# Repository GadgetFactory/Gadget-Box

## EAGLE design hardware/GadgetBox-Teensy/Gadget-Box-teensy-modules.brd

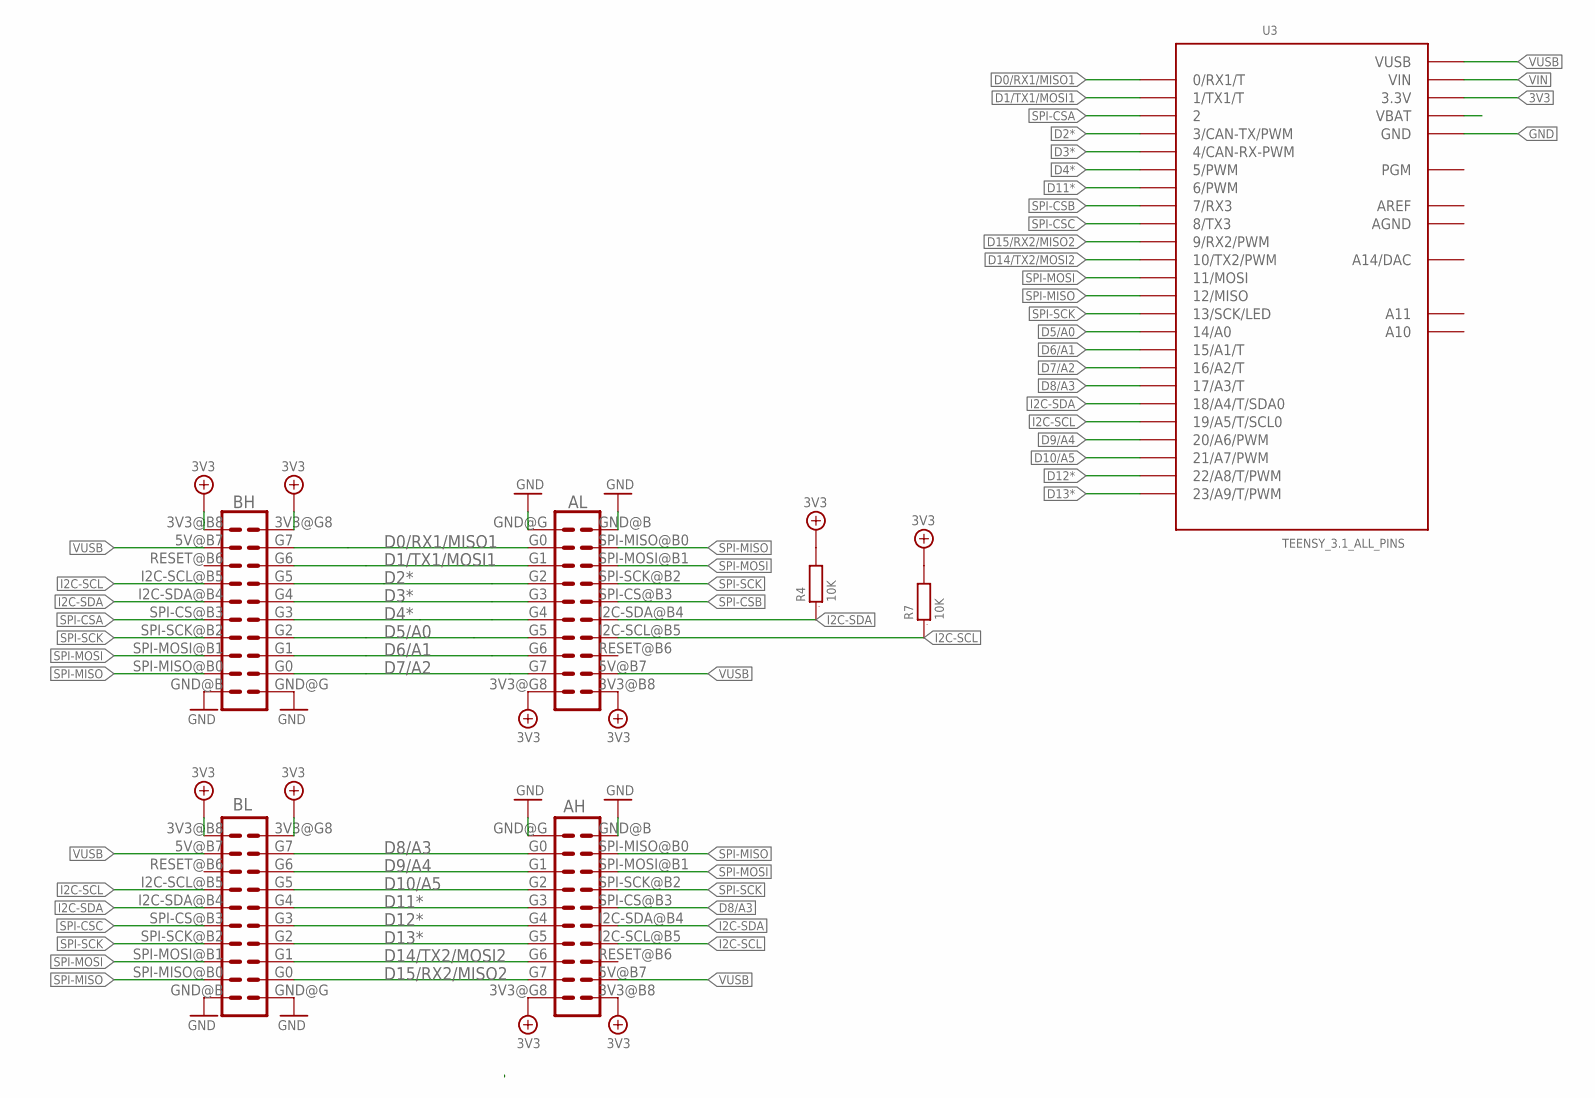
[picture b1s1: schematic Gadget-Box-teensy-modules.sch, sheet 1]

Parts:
AH: ECOGECOG_SLOT_ALT1; ECOG_ALT1; PARTNO PPPC102LFBN-RC,SULLINS CONNECTOR SOLUTI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
AL: ECOGECOG_SLOT_ALT1; ECOG_ALT1; PARTNO PPPC102LFBN-RC,SULLINS CONNECTOR SOLUTI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
BH: ECOGECOG_SLOT_ALT1; ECOG_ALT1; PARTNO PPPC102LFBN-RC,SULLINS CONNECTOR SOLUTI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
BL: ECOGECOG_SLOT_ALT1; ECOG_ALT1; PARTNO PPPC102LFBN-RC,SULLINS CONNECTOR SOLUTI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
R4, R7: 10K; 0603; PARTNO RC0603JR-0710KL,YAGEO (VA),dk,311-10KGR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
U3: TEENSY_3.1_ALL_PINS; TEENSY3-ALL_PINS

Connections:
3V3: AH.3V3@B8 (3V3), AH.3V3@G8 (3V3), AL.3V3@B8 (3V3), AL.3V3@G8 (3V3), BH.3V3@B8 (3V3), BH.3V3@G8 (3V3), BL.3V3@B8 (3V3), BL.3V3@G8 (3V3), R4.2, R7.2, U3.3.3V, U3.3.3V1 (3.3V)
AGND: U3.AGND
AREF: U3.AREF
D0/RX1/MISO1: AL.G0, BH.G7, U3.0 (0/RX1/T)
D1/TX1/MOSI1: AL.G1, BH.G6, U3.1 (1/TX1/T)
D2*: AL.G2, BH.G5, U3.3 (3/CAN-TX/PWM)
D3*: AL.G3, BH.G4, U3.4 (4/CAN-RX-PWM)
D4*: AL.G4, BH.G3, U3.5 (5/PWM)
D5/A0: AL.G5, BH.G2, U3.14/A0; also elsewhere on the board
D6/A1: AL.G6, BH.G1, U3.15/A1 (15/A1/T)
D7/A2: AL.G7, BH.G0, U3.16/A2 (16/A2/T)
D8/A3: AH.G0, AH.SPI-CS@B3 (SPI-CS), BL.G7, U3.17/A3 (17/A3/T)
D9/A4: AH.G1, BL.G6, U3.20/A6 (20/A6/PWM)
D10/A5: AH.G2, BL.G5, U3.21/A7 (21/A7/PWM)
D11*: AH.G3, BL.G4, U3.6 (6/PWM)
D12*: AH.G4, BL.G3, U3.22/A8 (22/A8/T/PWM)
D13*: AH.G5, BL.G2, U3.23/A9 (23/A9/T/PWM)
D14/TX2/MOSI2: AH.G6, BL.G1, U3.10 (10/TX2/PWM)
D15/RX2/MISO2: AH.G7, BL.G0, U3.9 (9/RX2/PWM)
GND: AH.GND@B (GND), AH.GND@G (GND), AL.GND@B (GND), AL.GND@G (GND), BH.GND@B (GND), BH.GND@G (GND), BL.GND@B (GND), BL.GND@G (GND), U3.GND, U3.GND1 (GND); also elsewhere on the board
I2C-SCL: AH.I2C-SCL@B5 (I2C-SCL), AL.I2C-SCL@B5 (I2C-SCL), BH.I2C-SCL@B5 (I2C-SCL), BL.I2C-SCL@B5 (I2C-SCL), R7.1, U3.19/A5 (19/A5/T/SCL0)
I2C-SDA: AH.I2C-SDA@B4 (I2C-SDA), AL.I2C-SDA@B4 (I2C-SDA), BH.I2C-SDA@B4 (I2C-SDA), BL.I2C-SDA@B4 (I2C-SDA), R4.1, U3.18/A4 (18/A4/T/SDA0)
SPI-CSA: BH.SPI-CS@B3 (SPI-CS), U3.2
SPI-CSB: AL.SPI-CS@B3 (SPI-CS), U3.7 (7/RX3)
SPI-CSC: BL.SPI-CS@B3 (SPI-CS), U3.8 (8/TX3)
SPI-MISO: AH.SPI-MISO@B0 (SPI-MISO), AL.SPI-MISO@B0 (SPI-MISO), BH.SPI-MISO@B0 (SPI-MISO), BL.SPI-MISO@B0 (SPI-MISO), U3.12 (12/MISO)
SPI-MOSI: AH.SPI-MOSI@B1 (SPI-MOSI), AL.SPI-MOSI@B1 (SPI-MOSI), BH.SPI-MOSI@B1 (SPI-MOSI), BL.SPI-MOSI@B1 (SPI-MOSI), U3.11 (11/MOSI)
SPI-SCK: AH.SPI-SCK@B2 (SPI-SCK), AL.SPI-SCK@B2 (SPI-SCK), BH.SPI-SCK@B2 (SPI-SCK), BL.SPI-SCK@B2 (SPI-SCK), U3.13 (13/SCK/LED)
VBAT: U3.VBAT
VIN: U3.VIN; also elsewhere on the board
VUSB: AH.5V@B7 (5V), AL.5V@B7 (5V), BH.5V@B7 (5V), BL.5V@B7 (5V), U3.VUSB; also elsewhere on the board

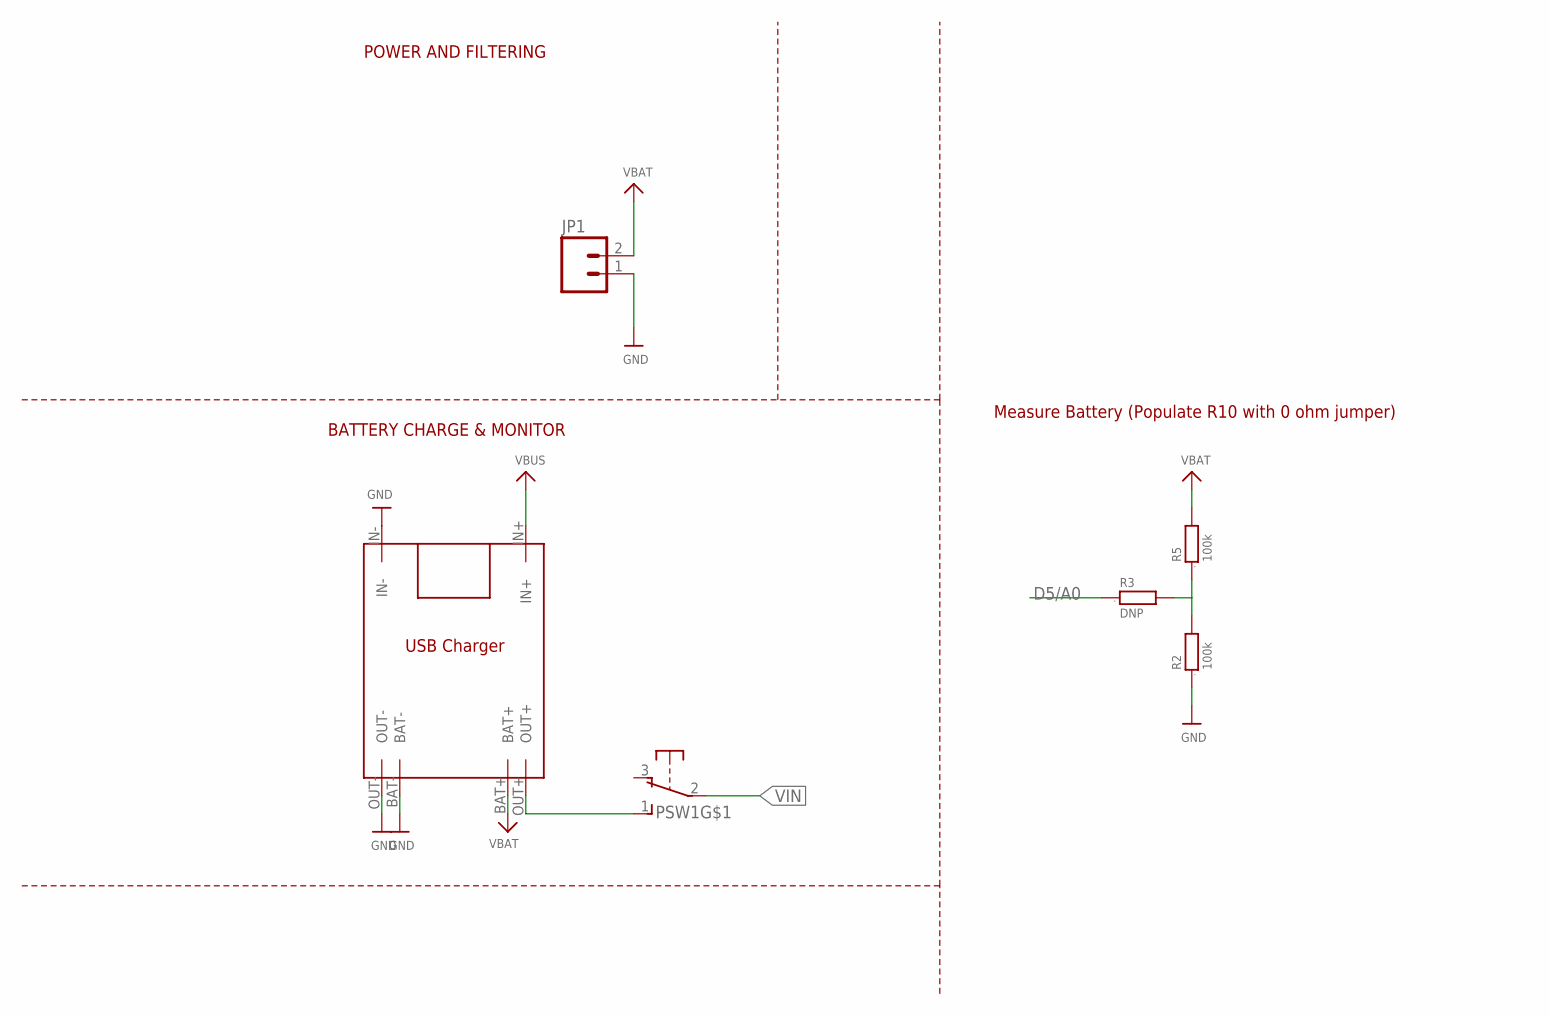
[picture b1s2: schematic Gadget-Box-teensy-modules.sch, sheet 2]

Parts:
JP1: M02-JST-2-PTH-NO_SILK; JST-2-PTH-NS; PARTNO B2B-PH-SM4-TB(LF)(SN),JST SALES AMERICA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
PSW1: OS102011MA1Q; PARTNO OS102011MA1QN1,C&K Components,dk,CKN955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
R2, R5: 100k; 0603; PARTNO RC0603JR-07100KL,YAGEO (VA),dk,311-100K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
R3: DNP; 0603
U$1: TP4056

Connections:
D5/A0: R3.1; also elsewhere on the board
GND: JP1.1, R2.1, U$1.BAT-, U$1.IN-, U$1.OUT-; also elsewhere on the board
unnamed: R2.2, R3.2, R5.1
VBATTTERY: JP1.2, R5.2, U$1.BAT+
VIN: PSW1.2; also elsewhere on the board
VOUT: PSW1.1 (S), U$1.OUT+
VUSB: U$1.IN+; also elsewhere on the board

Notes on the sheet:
POWER AND FILTERING
BATTERY CHARGE & MONITOR
Measure Battery (Populate R10 with 0 ohm jumper)

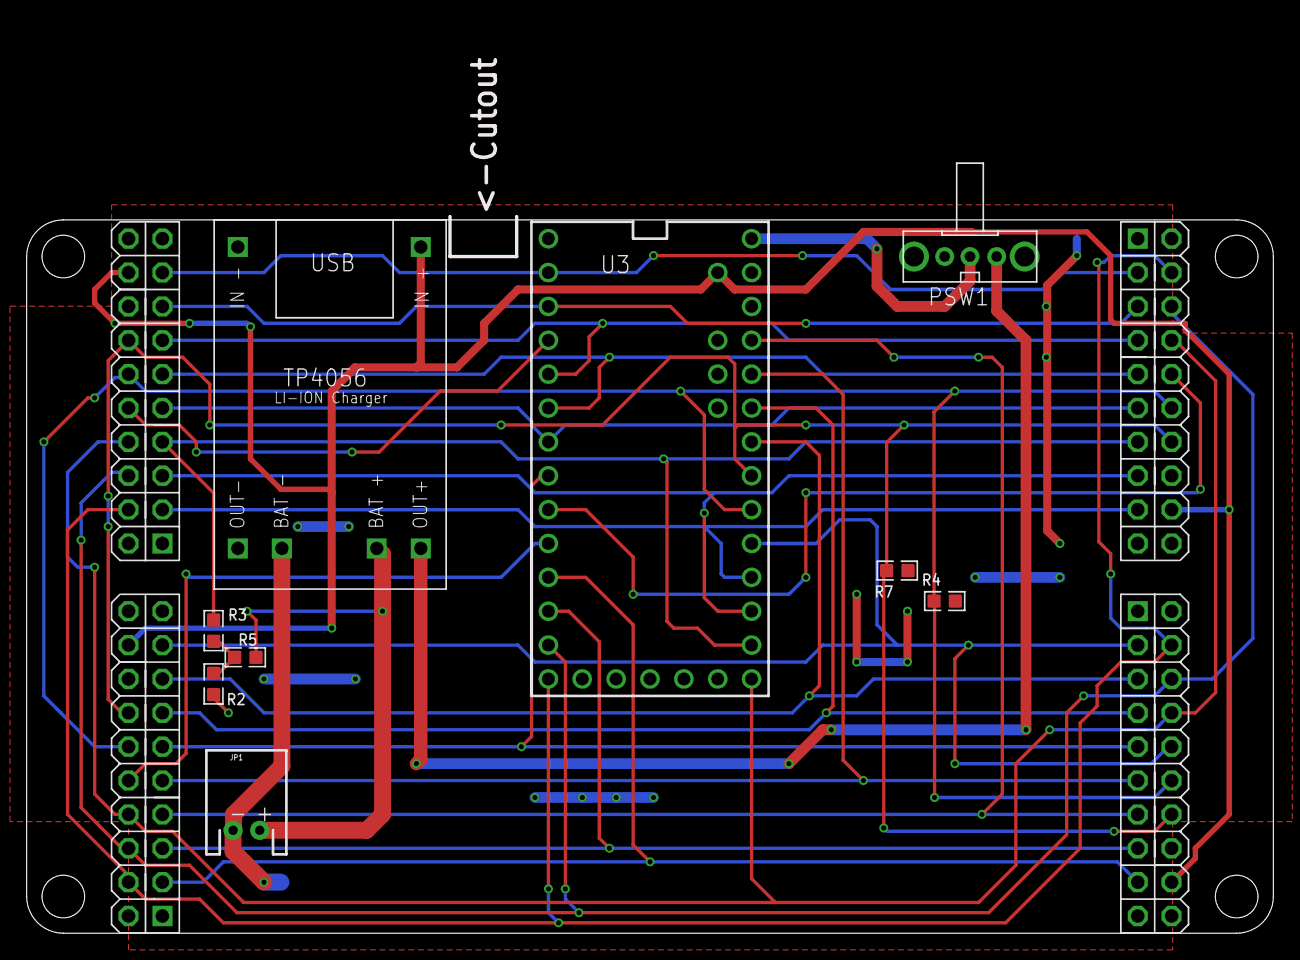
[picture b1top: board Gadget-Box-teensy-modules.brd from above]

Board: 2 copper layers, 93.2 x 67.7 mm, 15 parts (1 on the bottom side), 31 nets.

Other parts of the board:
$$U$1: ECOG93P53P5
U$100: GADGETBOX_TEXT

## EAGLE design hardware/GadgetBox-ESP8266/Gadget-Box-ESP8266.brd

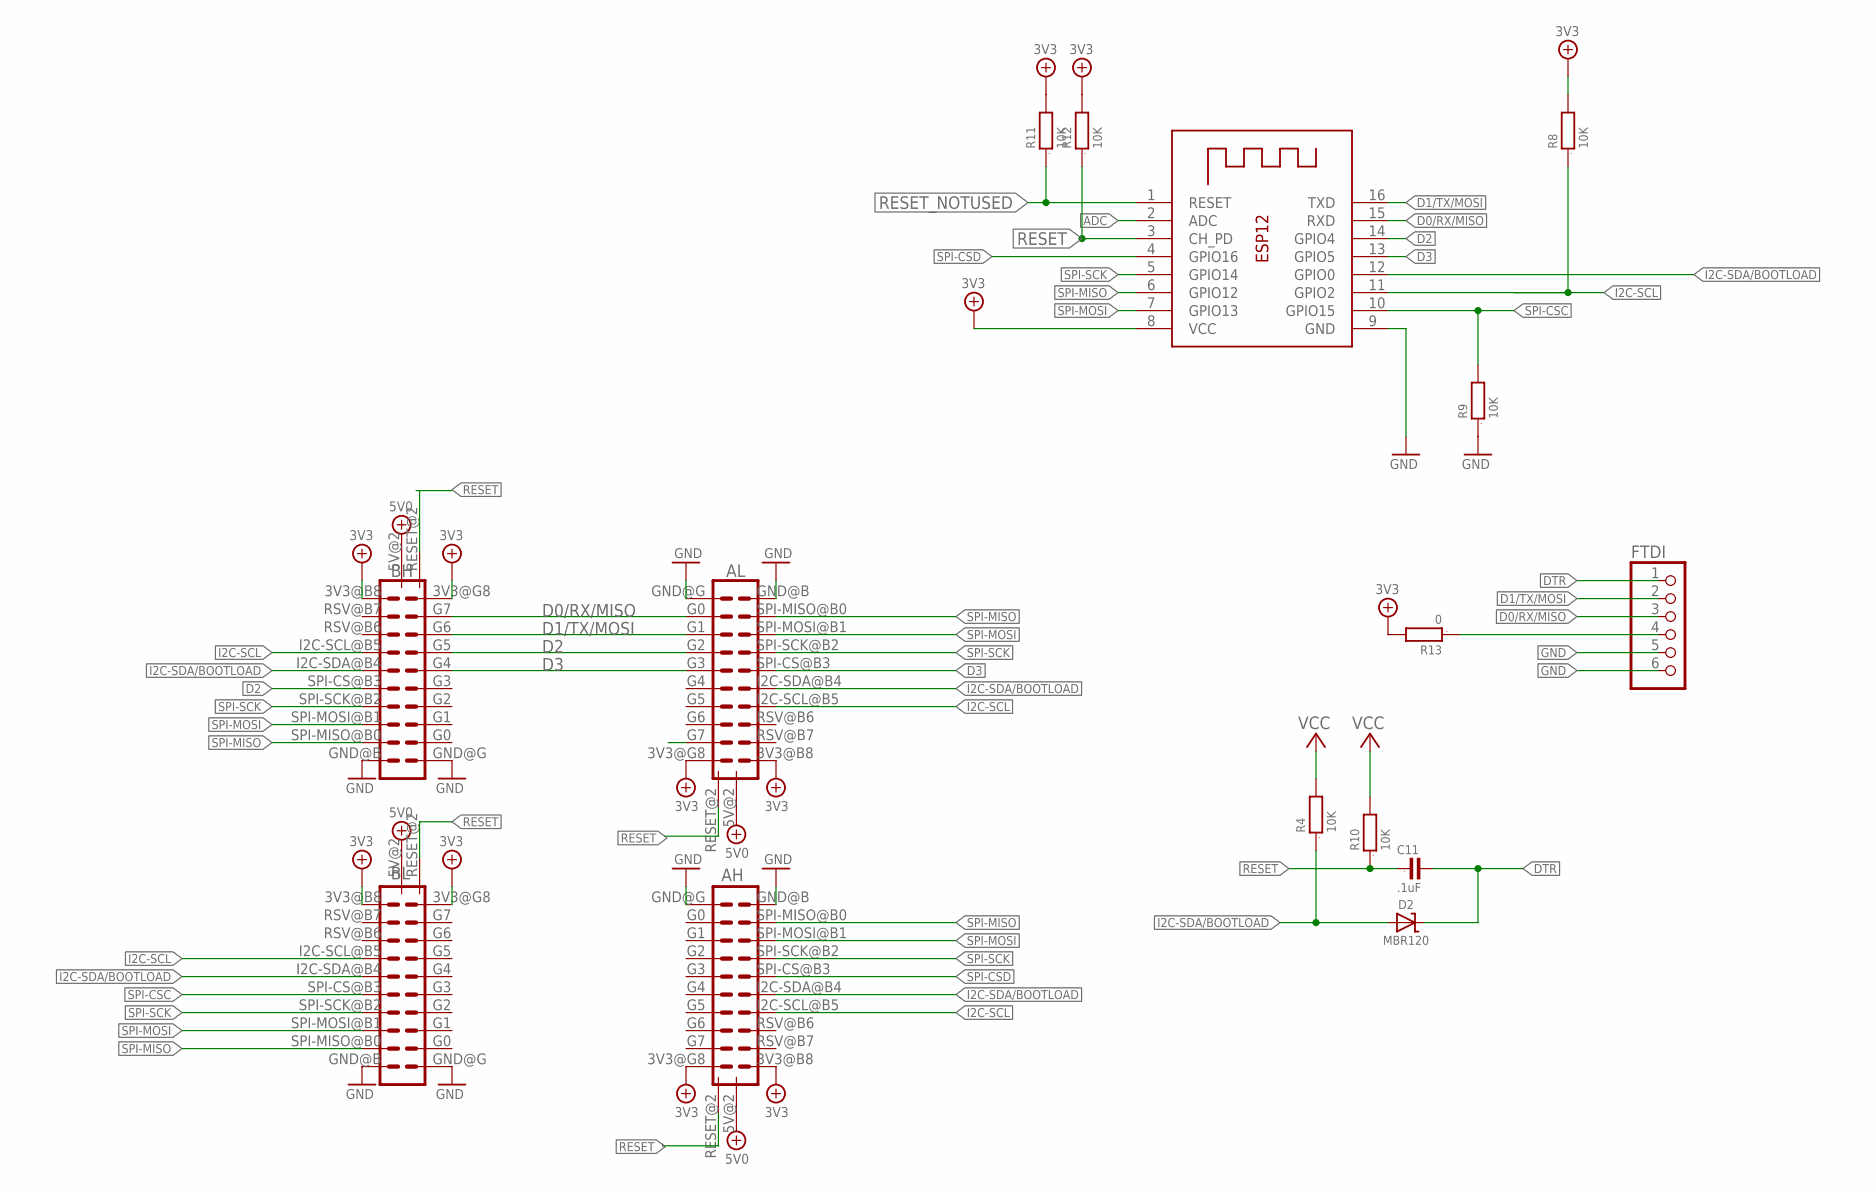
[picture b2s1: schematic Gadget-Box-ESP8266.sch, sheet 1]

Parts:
AH: ECOGECOG_SLOT_ALT1; ECOG_ALT1; PARTNO PPPC102LFBN-RC,SULLINS CONNECTOR SOLUTI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
AL: ECOGECOG_SLOT_ALT1; ECOG_ALT1; PARTNO PPPC102LFBN-RC,SULLINS CONNECTOR SOLUTI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
BH: ECOGECOG_SLOT_ALT1; ECOG_ALT1; PARTNO PPPC102LFBN-RC,SULLINS CONNECTOR SOLUTI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
BL: ECOGECOG_SLOT_ALT1; ECOG_ALT1; PARTNO PPPC102LFBN-RC,SULLINS CONNECTOR SOLUTI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
C11: .1uF; 0805; PARTNO GRM21BR71E104KA01L,MURATA ELECTRONICS (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
D2: MBR120; SOD-123; PARTNO MBR120VLSFT3G,on semiconductor,dk,MBR12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
FTDI: PINHD-1X6; 1X06; PARTNO PPPC061LGBN-RC,SULLINS CONNECTOR SOLUTI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
R4, R10: 10K; 0805; PARTNO RC0805JR-0710KL,YAGEO (VA),dk,311-10KAR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
R8, R9, R11, R12: 10K; 0805; PARTNO RC0805JR-0710KL,YAGEO (VA),dk,311-10KAR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; DIGIKEY RMCF0805JT10K0CT-ND
R13: 0; 0805
X2: ESP-12; PARTNO 385646,AI-Thinker,dx.com,385646,ESP8266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

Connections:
3V3: AH.3V3@B8 (3V3), AH.3V3@G8 (3V3), AL.3V3@B8 (3V3), AL.3V3@G8 (3V3), BH.3V3@B8 (3V3), BH.3V3@G8 (3V3), BL.3V3@B8 (3V3), BL.3V3@G8 (3V3), R8.2, R10.2, R11.2, R12.2, R13.2, X2.8 (VCC); also elsewhere on the board
5V0: AH.5V@2 (5V), AL.5V@2 (5V), BH.5V@2 (5V), BL.5V@2 (5V); also elsewhere on the board
ADC: X2.2 (ADC); also elsewhere on the board
D0/RX/MISO: AL.G0, BH.G7, FTDI.3, X2.15 (RXD)
D1/TX/MOSI: AL.G1, BH.G6, FTDI.2, X2.16 (TXD)
D2: AL.G2, BH.G5, BH.SPI-CS@B3 (SPI-CS), X2.14 (GPIO4)
D3: AL.G3, AL.SPI-CS@B3 (SPI-CS), BH.G4, X2.13 (GPIO5)
DTR: C11.2, D2.C, FTDI.1
GND: AH.GND@B (GND), AH.GND@G (GND), AL.GND@B (GND), AL.GND@G (GND), BH.GND@B (GND), BH.GND@G (GND), BL.GND@B (GND), BL.GND@G (GND), FTDI.5, FTDI.6, R9.1, X2.9 (GND); also elsewhere on the board
I2C-SCL: AH.I2C-SCL@B5 (I2C-SCL), AL.I2C-SCL@B5 (I2C-SCL), BH.I2C-SCL@B5 (I2C-SCL), BL.I2C-SCL@B5 (I2C-SCL), R8.1, X2.11 (GPIO2)
I2C-SDA/BOOTLOAD: AH.I2C-SDA@B4 (I2C-SDA), AL.I2C-SDA@B4 (I2C-SDA), BH.I2C-SDA@B4 (I2C-SDA), BL.I2C-SDA@B4 (I2C-SDA), D2.A, R4.1, X2.12 (GPIO0)
unnamed: FTDI.4, R13.1
RESET: AH.RESET@2 (RESET), AL.RESET@2 (RESET), BH.RESET@2 (RESET), BL.RESET@2 (RESET), C11.1, R10.1, R12.1, X2.3 (CH_PD)
RESET_NOTUSED: R11.1, X2.1 (RESET)
SPI-CSC: BL.SPI-CS@B3 (SPI-CS), R9.2, X2.10 (GPIO15)
SPI-CSD: AH.SPI-CS@B3 (SPI-CS), X2.4 (GPIO16)
SPI-MISO: AH.SPI-MISO@B0 (SPI-MISO), AL.SPI-MISO@B0 (SPI-MISO), BH.SPI-MISO@B0 (SPI-MISO), BL.SPI-MISO@B0 (SPI-MISO), X2.6 (GPIO12)
SPI-MOSI: AH.SPI-MOSI@B1 (SPI-MOSI), AL.SPI-MOSI@B1 (SPI-MOSI), BH.SPI-MOSI@B1 (SPI-MOSI), BL.SPI-MOSI@B1 (SPI-MOSI), X2.7 (GPIO13)
SPI-SCK: AH.SPI-SCK@B2 (SPI-SCK), AL.SPI-SCK@B2 (SPI-SCK), BH.SPI-SCK@B2 (SPI-SCK), BL.SPI-SCK@B2 (SPI-SCK), X2.5 (GPIO14)
VCC: R4.2

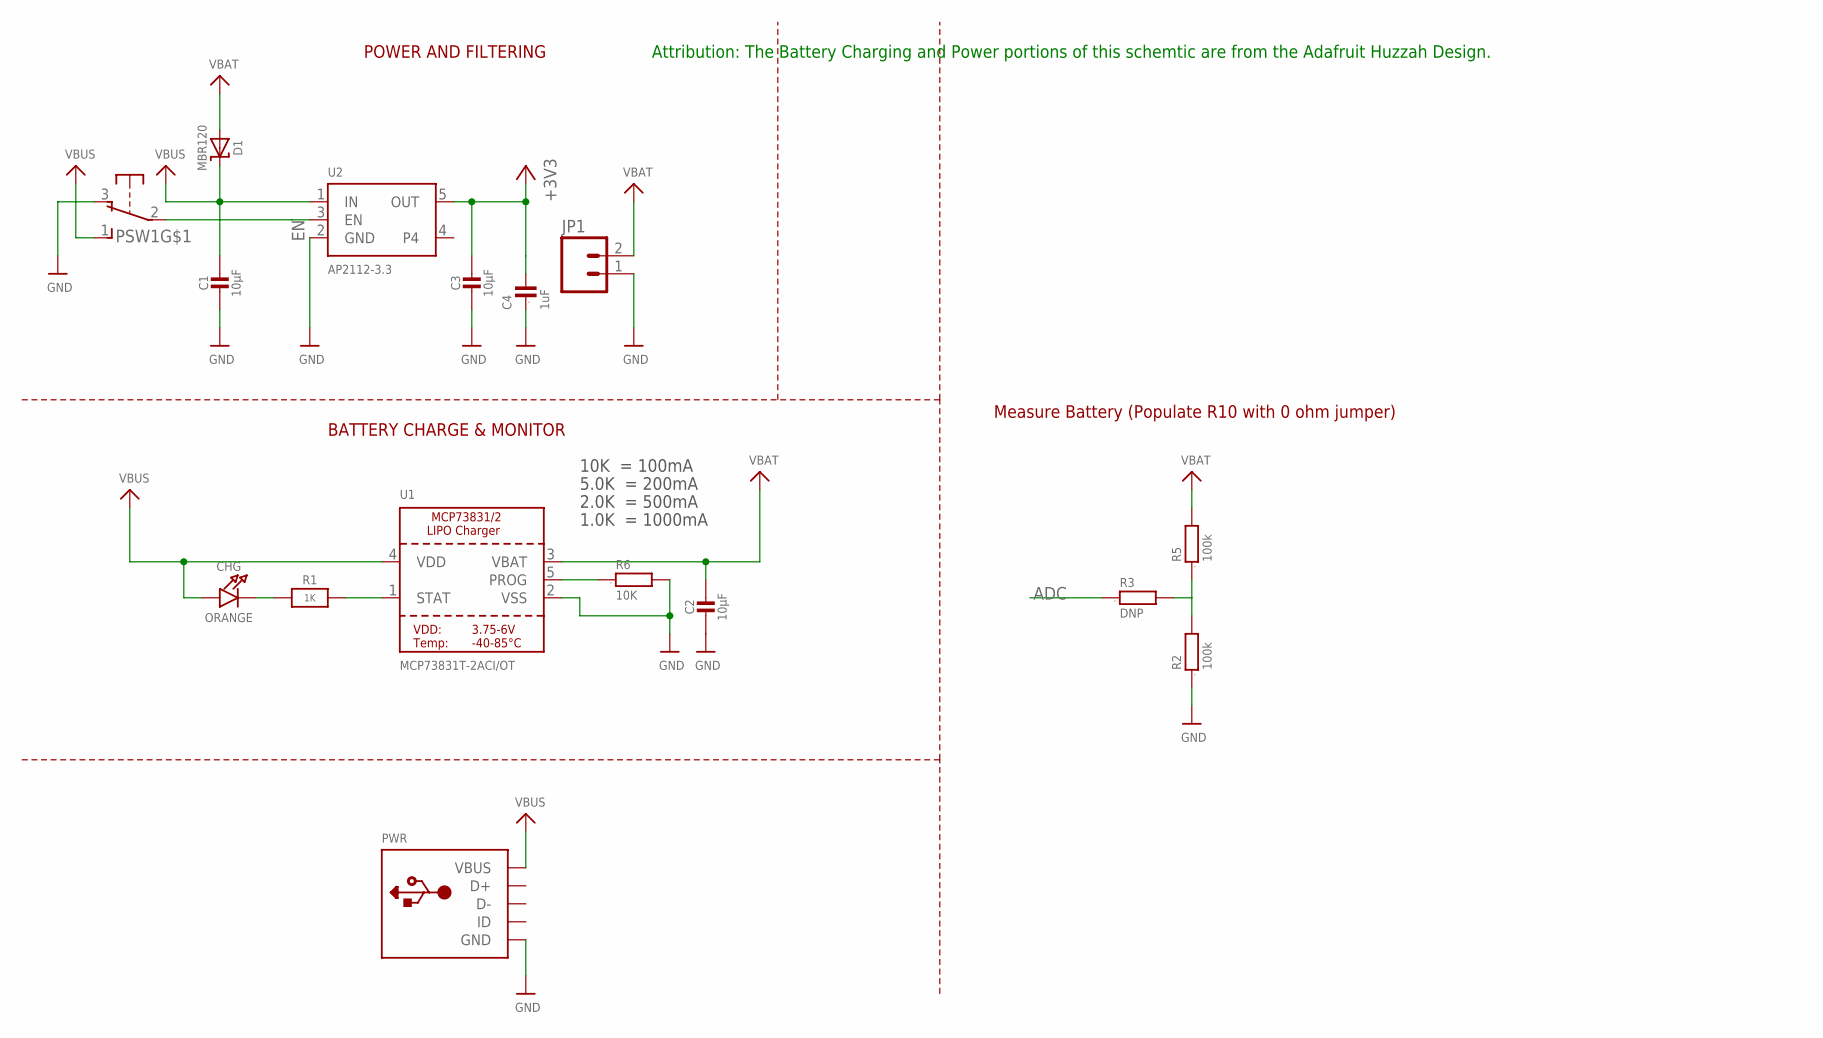
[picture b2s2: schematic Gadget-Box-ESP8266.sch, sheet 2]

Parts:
C1, C2, C3: 10µF; 0805-NO; PARTNO CL21F106ZPFNNNE,Samsung,DK,1276-3012-1-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
C4: 1uF; 0603; PARTNO C1608X5R1A105K080AC,TDK CORPORATION (VA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
CHG: ORANGE; CHIPLED_0805_NOOUTLINE; PARTNO LTST-C171EKT,LITE-ON INC (VA),DK,160-14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
D1: MBR120; SOD-123; PARTNO MBR120VLSFT3G,on semiconductor,dk,MBR12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
JP1: M02-JST-2-PTH-NO_SILK; JST-2-PTH-NS; PARTNO B2B-PH-SM4-TB(LF)(SN),JST SALES AMERICA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
PSW1: OS102011MA1Q; PARTNO OS102011MA1QN1,C&K Components,dk,CKN955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
PWR: USBMINIB; USB-MINIB; PARTNO USB-M26FTR,On Shore Technology Inc,DK,E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
R1: 1K; 0603-NO; PARTNO RC0603JR-071KL,YAGEO (VA),dk,311-1.0KGR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
R2, R5: 100k; 0603; PARTNO RC0603JR-07100KL,YAGEO (VA),dk,311-100K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
R3: DNP; 0603
R6: 10K; 0805; PARTNO RC0805JR-0710KL,YAGEO (VA),dk,311-10KAR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
U1: MCP73831T-2ACI/OT; SOT23-5; PARTNO MCP73831T-2ACI/OT,MICROCHIP TECHNOLOGY 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
U2: AP2112-3.3; SOT23-5; PARTNO AP2112K-3.3TRG1,Diodes Incorporated,dk,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

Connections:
3V3: C3.1, C4.2, U2.5 (OUT); also elsewhere on the board
5V0: C1.1, CHG.A, D1.C, PSW1.1 (S), PWR.VBUS, U1.4 (VDD), U2.1 (IN); also elsewhere on the board
ADC: R3.1; also elsewhere on the board
EN: PSW1.2, U2.3 (EN)
GND: C1.2, C2.2, C3.2, C4.1, JP1.1, PSW1.3 (O), PWR.GND, R2.1, R6.2, U1.2 (VSS), U2.2 (GND); also elsewhere on the board
unnamed: CHG.C, R1.1
unnamed: R2.2, R3.2, R5.1
unnamed: R1.2, U1.1 (STAT)
unnamed: R6.1, U1.5 (PROG)
VBAT: C2.1, D1.A, JP1.2, R5.2, U1.3 (VBAT)

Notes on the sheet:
POWER AND FILTERING
10K = 100mA
5.0K = 200mA
2.0K = 500mA
1.0K = 1000mA
BATTERY CHARGE & MONITOR
Measure Battery (Populate R10 with 0 ohm jumper)
Attribution: The Battery Charging and Power portions of this schemtic are from the Adafruit Huzzah Design.

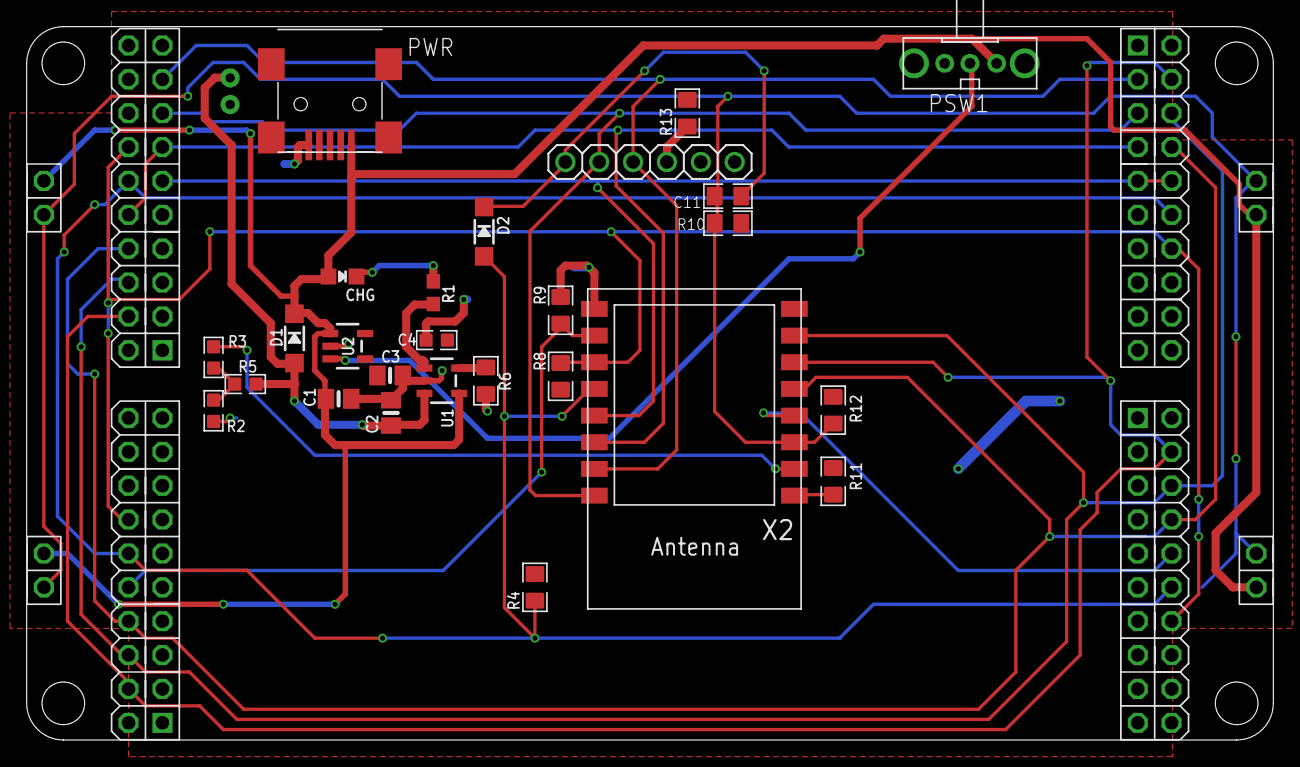
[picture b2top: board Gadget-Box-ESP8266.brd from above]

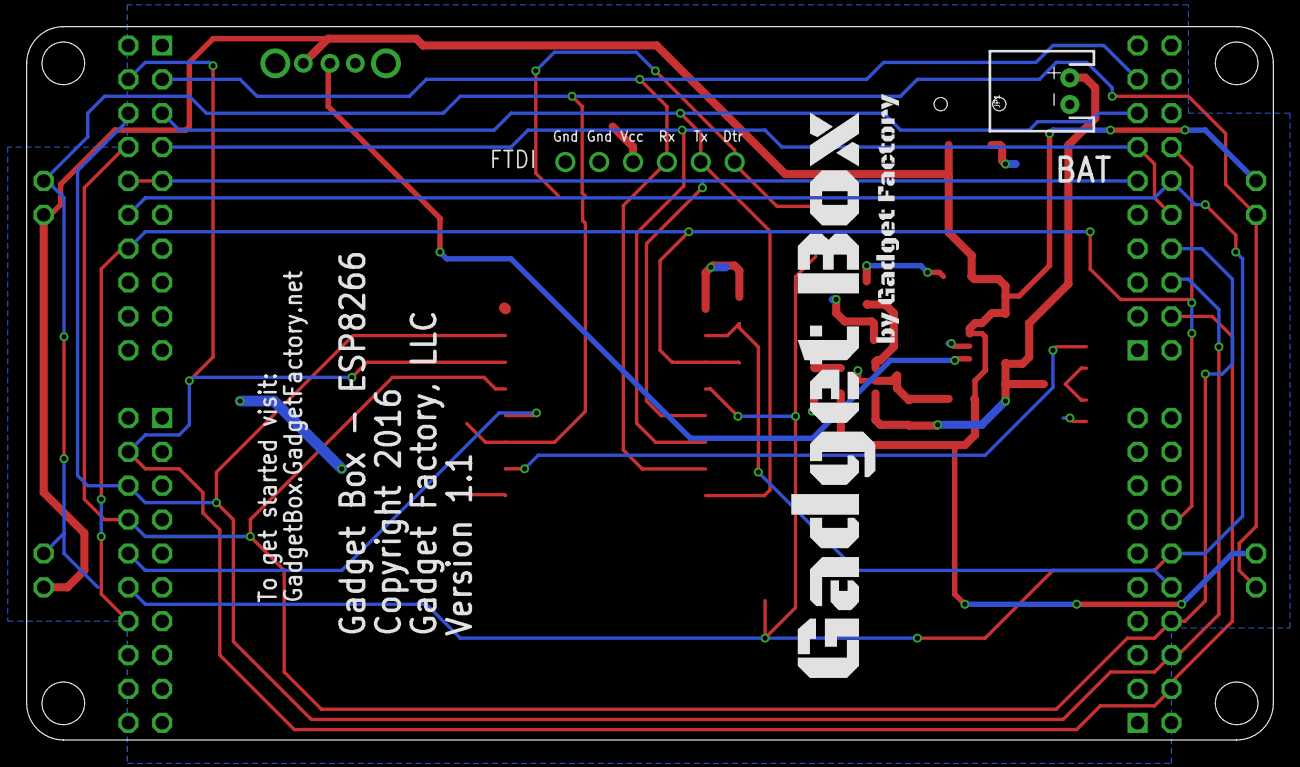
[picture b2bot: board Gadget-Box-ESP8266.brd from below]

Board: 2 copper layers, 93.5 x 53.5 mm, 33 parts (2 on the bottom side), 25 nets.

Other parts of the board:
$$U$1: ECOG93P53P5
U$100: GADGETBOX_TEXT

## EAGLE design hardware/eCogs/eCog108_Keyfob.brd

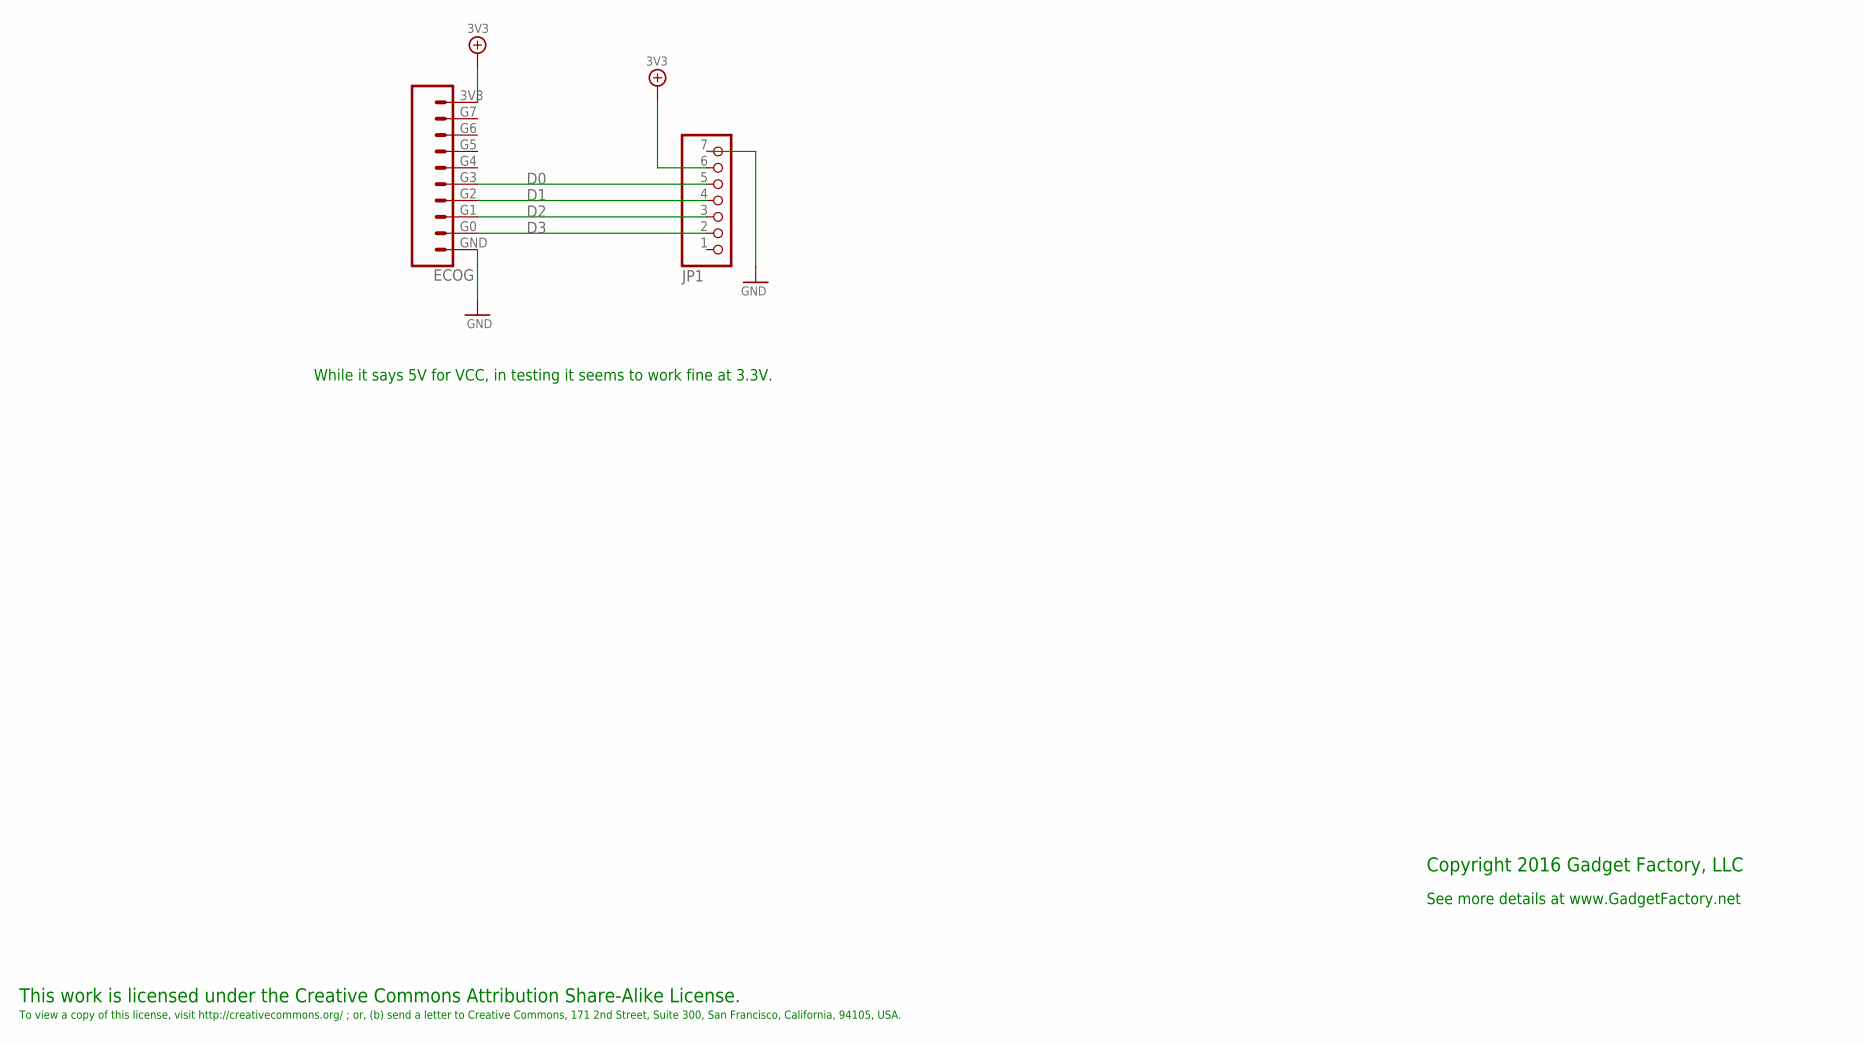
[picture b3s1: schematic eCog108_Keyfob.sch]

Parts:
ECOG: ECOG_GENERAL_ROWECOG_GENERAL_SMD; ECOG_GENERAL_SMD
JP1: PINHD-1X7; 1X07

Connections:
3V3: ECOG.3V3, JP1.6
D0: ECOG.G3, JP1.5
D1: ECOG.G2, JP1.4
D2: ECOG.G1, JP1.3
D3: ECOG.G0, JP1.2
GND: ECOG.GND, JP1.7

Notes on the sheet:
This work is licensed under the Creative Commons Attribution Share-Alike License.
To view a copy of this license, visit http://creativecommons.org/ ; or, (b) send a letter to Creative Commons, 171 2nd Street, Suite 300, San Francisco, California, 94105, USA.
Copyright 2016 Gadget Factory, LLC
See more details at www.GadgetFactory.net
While it says 5V for VCC, in testing it seems to work fine at 3.3V.

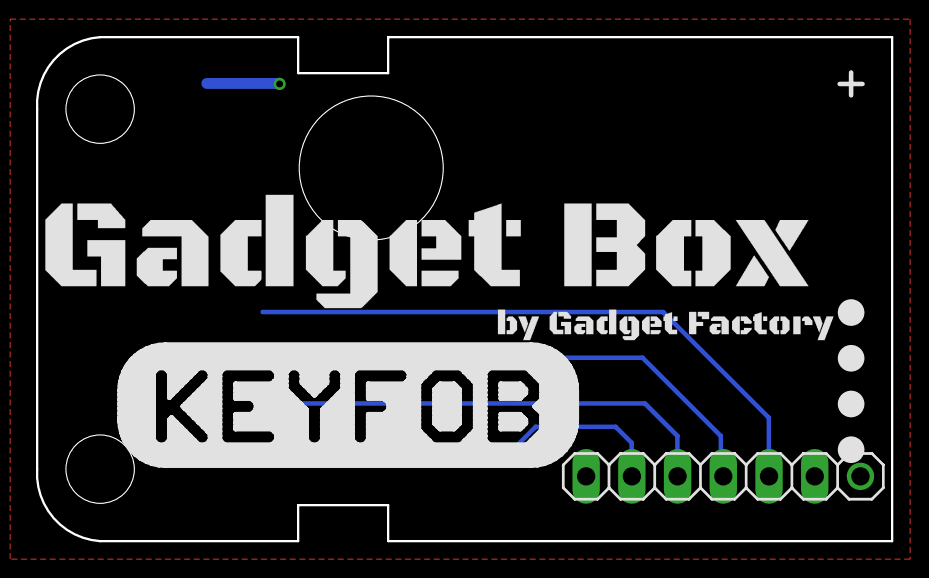
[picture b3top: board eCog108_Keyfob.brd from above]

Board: 2 copper layers, 47.5 x 28.0 mm, 7 parts (0 on the bottom side), 6 nets.

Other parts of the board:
U$1: GADGETBOX_TEXT
U$2, U$3, U$4, U$5: LEGEND_DIO

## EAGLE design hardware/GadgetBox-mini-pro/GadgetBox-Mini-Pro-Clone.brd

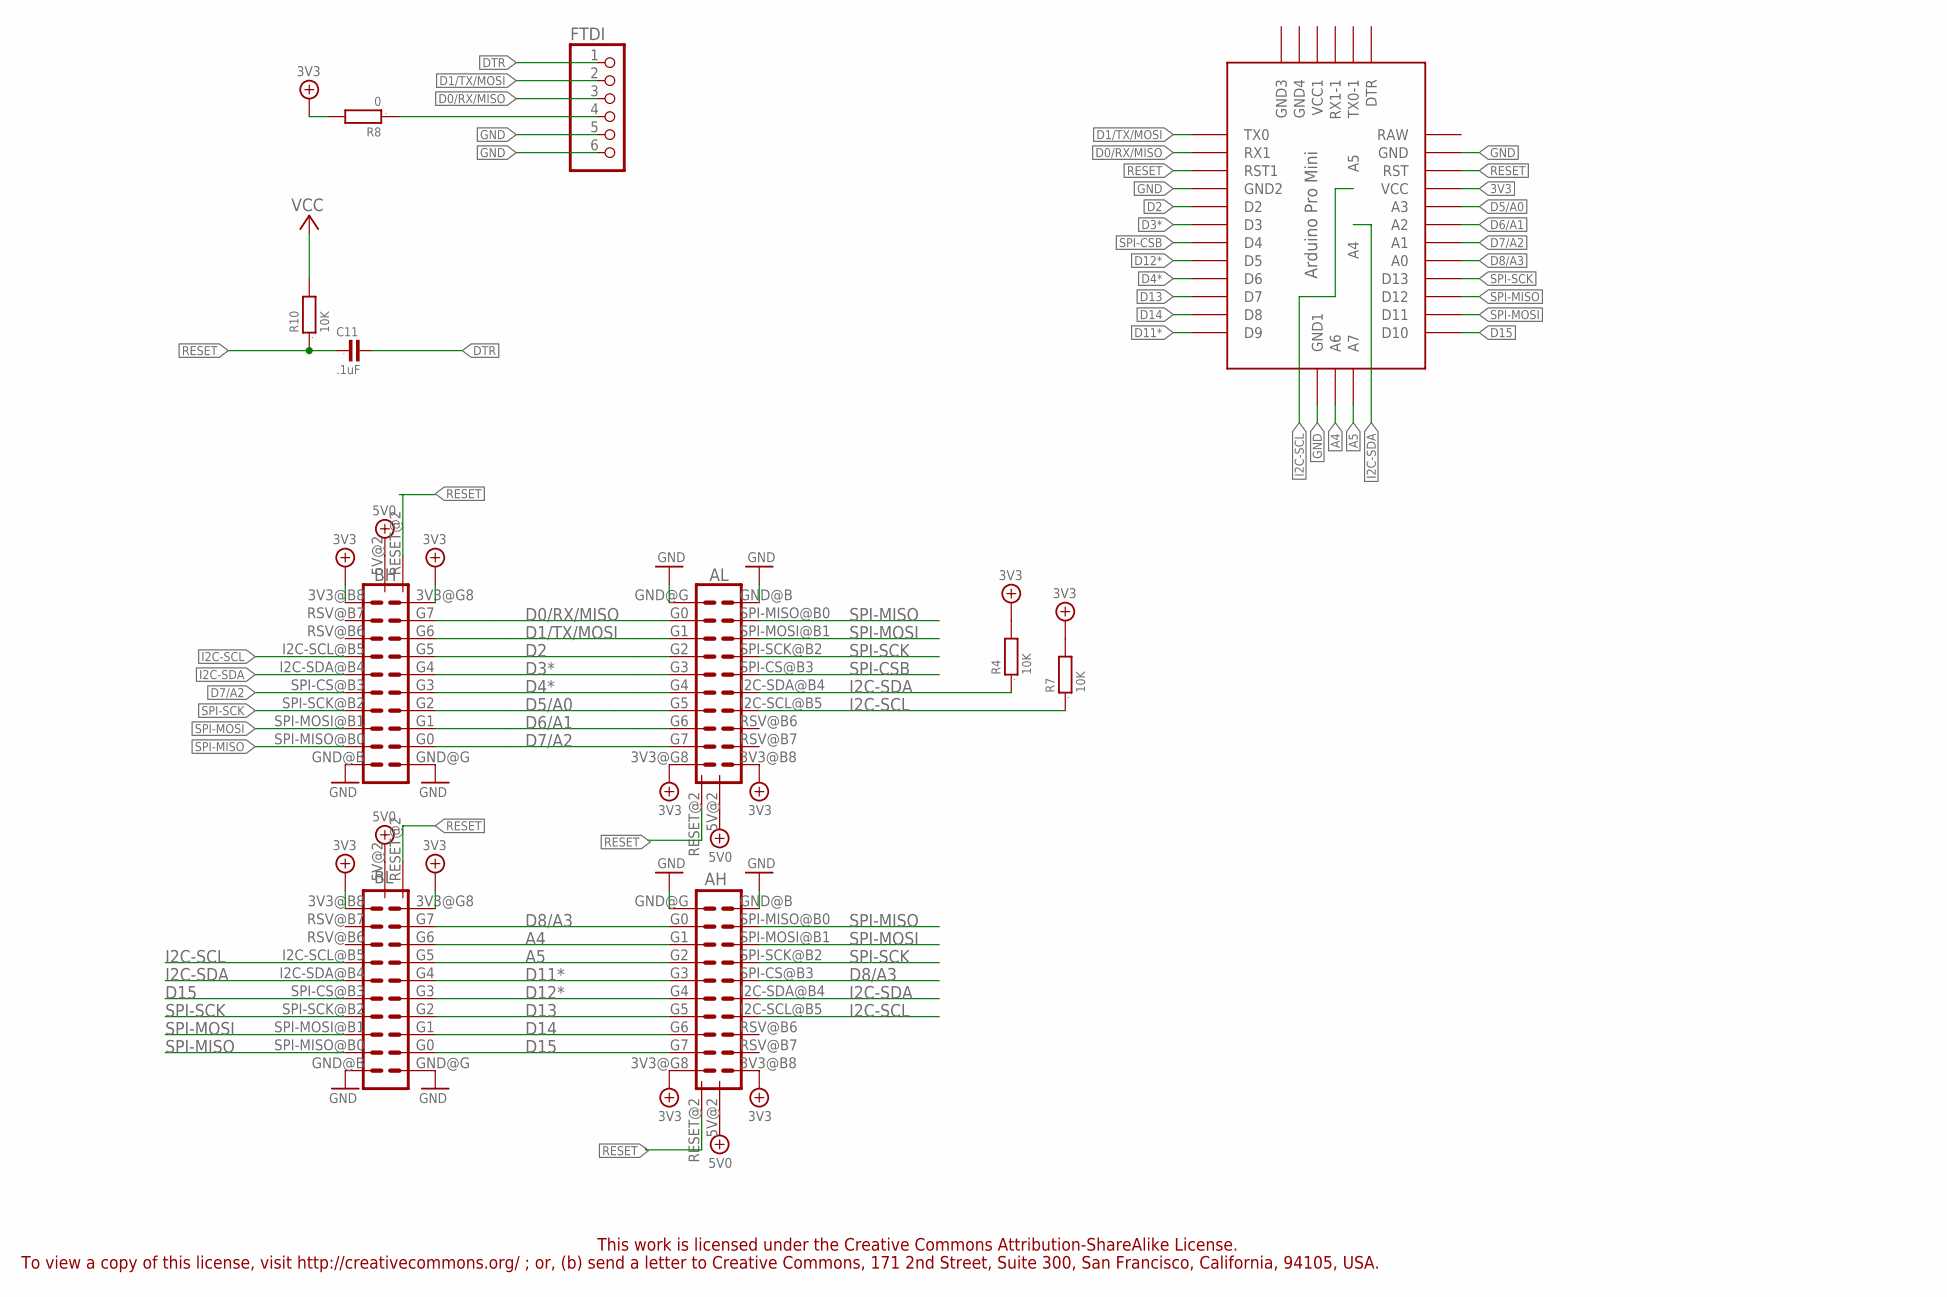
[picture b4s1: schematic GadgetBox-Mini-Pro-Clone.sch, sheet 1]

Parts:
AH: ECOGECOG_SLOT_ALT1; ECOG_ALT1; PARTNO PPPC102LFBN-RC,SULLINS CONNECTOR SOLUTI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
AL: ECOGECOG_SLOT_ALT1; ECOG_ALT1; PARTNO PPPC102LFBN-RC,SULLINS CONNECTOR SOLUTI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
BH: ECOGECOG_SLOT_ALT1; ECOG_ALT1; PARTNO PPPC102LFBN-RC,SULLINS CONNECTOR SOLUTI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
BL: ECOGECOG_SLOT_ALT1; ECOG_ALT1; PARTNO PPPC102LFBN-RC,SULLINS CONNECTOR SOLUTI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
C11: .1uF; 0805; PARTNO GRM21BR71E104KA01L,MURATA ELECTRONICS (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
FTDI: PINHD-1X6; 1X06; PARTNO PPPC061LGBN-RC,SULLINS CONNECTOR SOLUTI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
R4, R7, R10: 10K; 0603; PARTNO RC0603JR-0710KL,YAGEO (VA),dk,311-10KGR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
R8: 0; 0603
U$1: ABK-PRO-MINI

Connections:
3V3: AH.3V3@B8 (3V3), AH.3V3@G8 (3V3), AL.3V3@B8 (3V3), AL.3V3@G8 (3V3), BH.3V3@B8 (3V3), BH.3V3@G8 (3V3), BL.3V3@B8 (3V3), BL.3V3@G8 (3V3), R4.2, R7.2, R8.2, R10.2, U$1.VCC; also elsewhere on the board
5V0: AH.5V@2 (5V), AL.5V@2 (5V), BH.5V@2 (5V), BL.5V@2 (5V); also elsewhere on the board
A4: AH.G1, BL.G6, U$1.A6
A5: AH.G2, BL.G5, U$1.A7
D0/RX/MISO: AL.G0, BH.G7, FTDI.3, U$1.RX1
D1/TX/MOSI: AL.G1, BH.G6, FTDI.2, U$1.TX0
D2: AL.G2, BH.G5, U$1.D2
D3*: AL.G3, BH.G4, U$1.D3
D4*: AL.G4, BH.G3, U$1.D6
D5/A0: AL.G5, BH.G2, U$1.A3; also elsewhere on the board
D6/A1: AL.G6, BH.G1, U$1.A2
D7/A2: AL.G7, BH.G0, BH.SPI-CS@B3 (SPI-CS), U$1.A1
D8/A3: AH.G0, AH.SPI-CS@B3 (SPI-CS), BL.G7, U$1.A0
D11*: AH.G3, BL.G4, U$1.D9
D12*: AH.G4, BL.G3, U$1.D5
D13: AH.G5, BL.G2, U$1.D7
D14: AH.G6, BL.G1, U$1.D8
D15: AH.G7, BL.G0, BL.SPI-CS@B3 (SPI-CS), U$1.D10
DTR: C11.2, FTDI.1
GND: AH.GND@B (GND), AH.GND@G (GND), AL.GND@B (GND), AL.GND@G (GND), BH.GND@B (GND), BH.GND@G (GND), BL.GND@B (GND), BL.GND@G (GND), FTDI.5, FTDI.6, U$1.GND, U$1.GND1 (GND2), U$1.GND4 (GND1); also elsewhere on the board
I2C-SCL: AH.I2C-SCL@B5 (I2C-SCL), AL.I2C-SCL@B5 (I2C-SCL), BH.I2C-SCL@B5 (I2C-SCL), BL.I2C-SCL@B5 (I2C-SCL), R7.1, U$1.A5
I2C-SDA: AH.I2C-SDA@B4 (I2C-SDA), AL.I2C-SDA@B4 (I2C-SDA), BH.I2C-SDA@B4 (I2C-SDA), BL.I2C-SDA@B4 (I2C-SDA), R4.1, U$1.A4
unnamed: FTDI.4, R8.1
RESET: AH.RESET@2 (RESET), AL.RESET@2 (RESET), BH.RESET@2 (RESET), BL.RESET@2 (RESET), C11.1, R10.1, U$1.RST, U$1.RST1
SPI-CSB: AL.SPI-CS@B3 (SPI-CS), U$1.D4
SPI-MISO: AH.SPI-MISO@B0 (SPI-MISO), AL.SPI-MISO@B0 (SPI-MISO), BH.SPI-MISO@B0 (SPI-MISO), BL.SPI-MISO@B0 (SPI-MISO), U$1.D12
SPI-MOSI: AH.SPI-MOSI@B1 (SPI-MOSI), AL.SPI-MOSI@B1 (SPI-MOSI), BH.SPI-MOSI@B1 (SPI-MOSI), BL.SPI-MOSI@B1 (SPI-MOSI), U$1.D11
SPI-SCK: AH.SPI-SCK@B2 (SPI-SCK), AL.SPI-SCK@B2 (SPI-SCK), BH.SPI-SCK@B2 (SPI-SCK), BL.SPI-SCK@B2 (SPI-SCK), U$1.D13

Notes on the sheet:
This work is licensed under the Creative Commons Attribution-ShareAlike License.
To view a copy of this license, visit http://creativecommons.org/ ; or, (b) send a letter to Creative Commons, 171 2nd Street, Suite 300, San Francisco, California, 94105, USA.

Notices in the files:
eCogs/eCog116_Pi_RGB_Matrix.brd:
CC0 STB
parts and their libraries:
SparkFun-Aesthetics: Licensing: CC v3.0 Share-Alike You are welcome to use this library for commercial purposes.
microbuilder: This work is placed in the public domain, and may be freely used for commercial and non-commercial work with the following conditions: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
